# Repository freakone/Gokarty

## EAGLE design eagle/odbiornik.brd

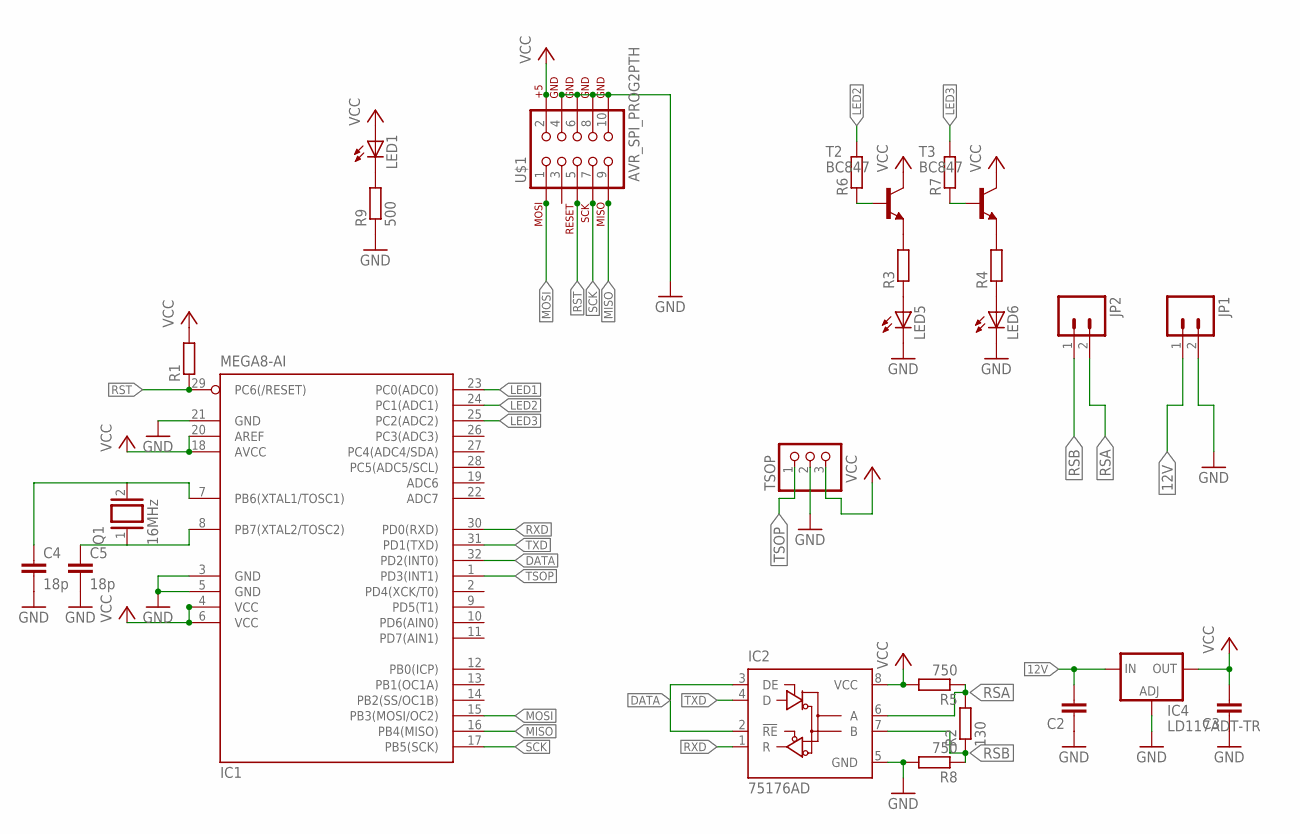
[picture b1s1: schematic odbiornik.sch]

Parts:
C2, C3: C-EUC0805; C0805
C4, C5: 18p; C0805
IC1: MEGA8-AI; TQFP32-08
IC2: 75176AD; D_R-PDSO-G8
IC4: LD117ADT-TR; DPACK
JP1, JP2: M02LOCK_LONGPADS; 1X02_LOCK_LONGPADS
LED1: LED1206; LED-1206
LED5, LED6: LEDSFH480; SFH480
Q1: 16MHz; QS
R1, R3, R4, R6, R7: R-EU_R0805; R0805
R2: 130; R0805
R5, R8: 750; R0805
R9: 500; R0805
T2, T3: BC847; SOT23
TSOP: PINHD-1X3; 1X03
U$1: AVR_SPI_PROG2PTH; AVR_ICSP

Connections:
12V: C2.2, IC4.3 (IN), JP1.1
DATA: IC1.32 (PD2(INT0)), IC2.2 (!RE), IC2.3 (DE)
GND: C2.1, C3.1, C4.2, C5.2, IC1.3 (GND), IC1.5 (GND), IC1.21 (GND), IC2.5 (GND), IC4.1 (ADJ), JP1.2, LED5.K (C), LED6.K (C), R8.2, R9.1, TSOP.2, U$1.4, U$1.6, U$1.8, U$1.10
LED1: IC1.23 (PC0(ADC0))
LED2: IC1.24 (PC1(ADC1)), R6.2
LED3: IC1.25 (PC2(ADC2)), R7.2
MISO: IC1.16 (PB4(MISO)), U$1.9
MOSI: IC1.15 (PB3(MOSI/OC2)), U$1.1
unnamed: LED1.C, R9.2
unnamed: LED5.A, R3.1
unnamed: LED6.A, R4.1
unnamed: R3.2, T2.2 (E)
unnamed: R4.2, T3.2 (E)
unnamed: R6.1, T2.1 (B)
unnamed: R7.1, T3.1 (B)
unnamed: C5.1, IC1.8 (PB7(XTAL2/TOSC2)), Q1.1
unnamed: C4.1, IC1.7 (PB6(XTAL1/TOSC1)), Q1.2
RSA: IC2.6 (A), JP2.2, R2.2, R5.1
RSB: IC2.7 (B), JP2.1, R2.1, R8.1
RST: IC1.29 (PC6(/RESET)), R1.1, U$1.5
RXD: IC1.30 (PD0(RXD)), IC2.1 (R)
SCK: IC1.17 (PB5(SCK)), U$1.7
TSOP: IC1.1 (PD3(INT1)), TSOP.1
TXD: IC1.31 (PD1(TXD)), IC2.4 (D)
VCC: C3.2, IC1.4 (VCC), IC1.6 (VCC), IC1.18 (AVCC), IC1.20 (AREF), IC2.8 (VCC), IC4.4 (OUT), LED1.A, R1.2, R5.2, T2.3 (C), T3.3 (C), TSOP.3, U$1.2

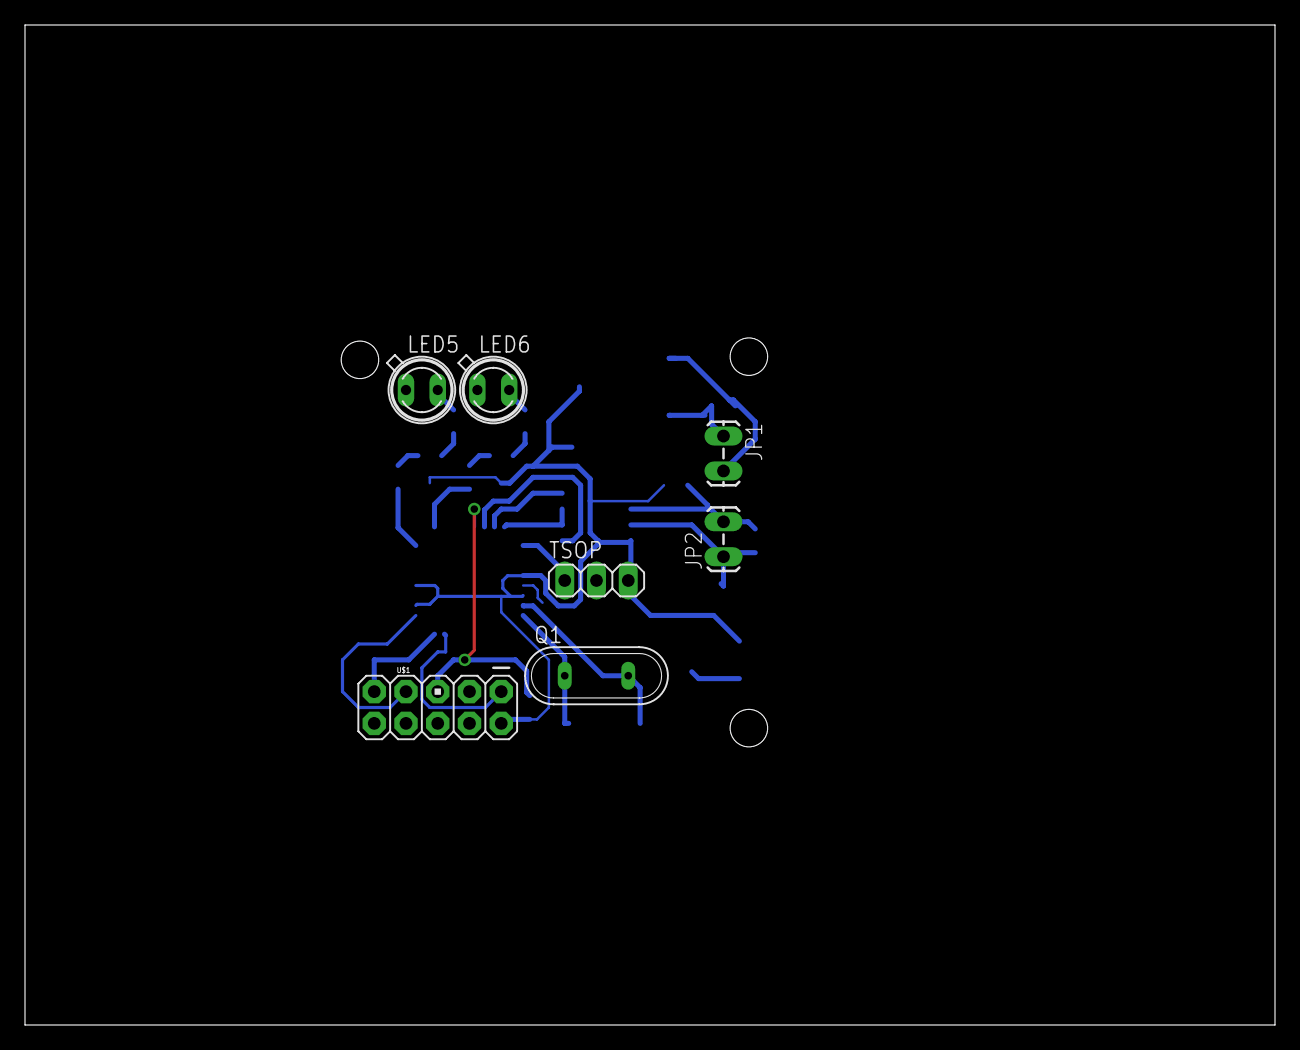
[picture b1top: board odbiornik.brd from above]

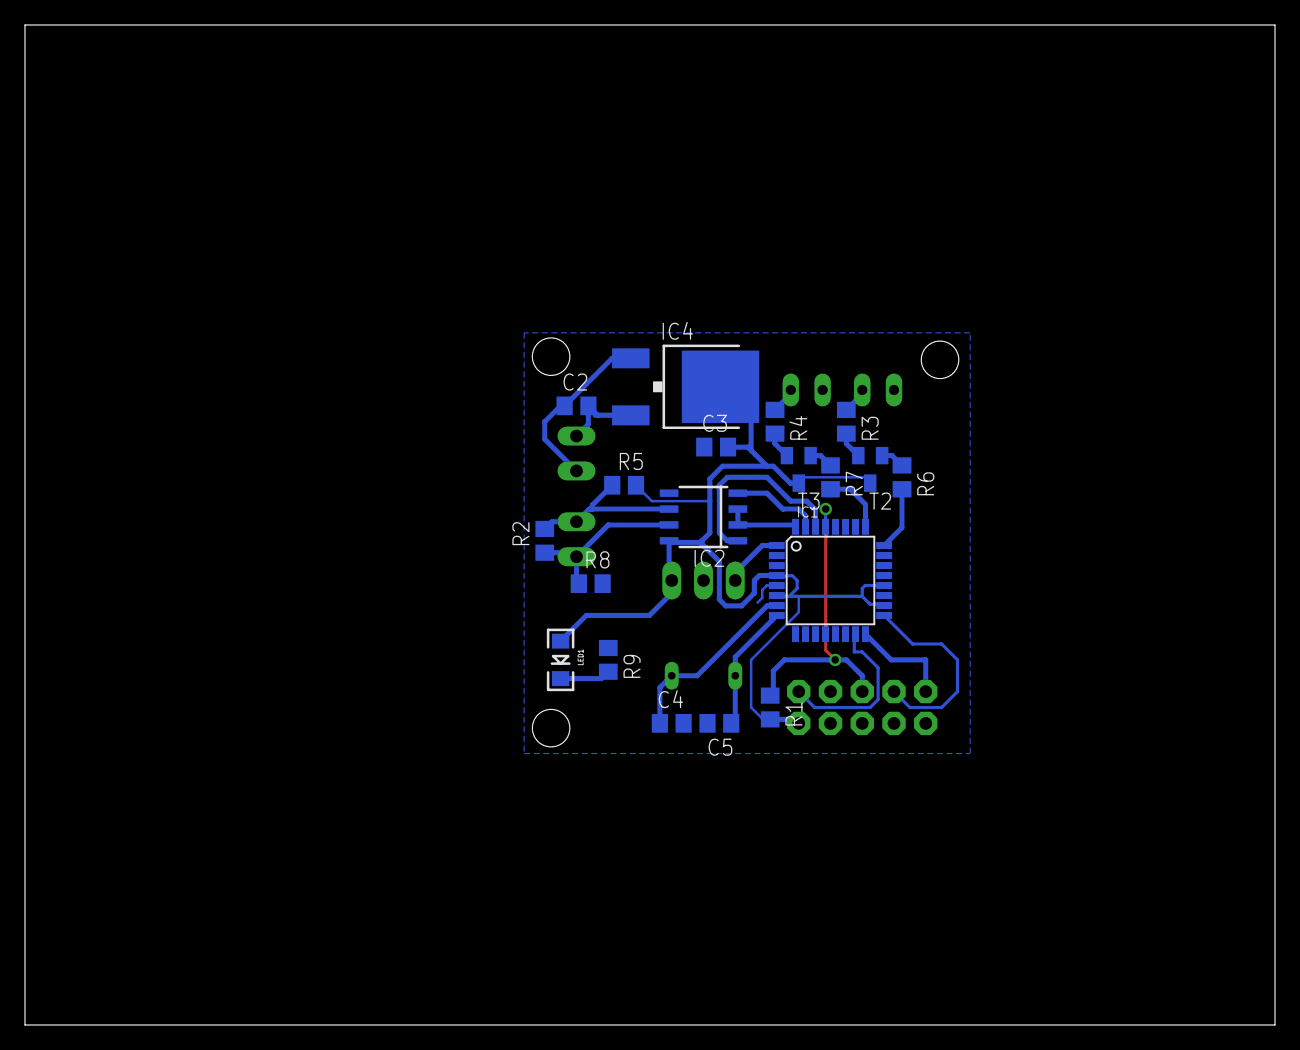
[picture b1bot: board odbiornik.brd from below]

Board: 2 copper layers, 100.0 x 80.0 mm, 26 parts (19 on the bottom side), 24 nets.

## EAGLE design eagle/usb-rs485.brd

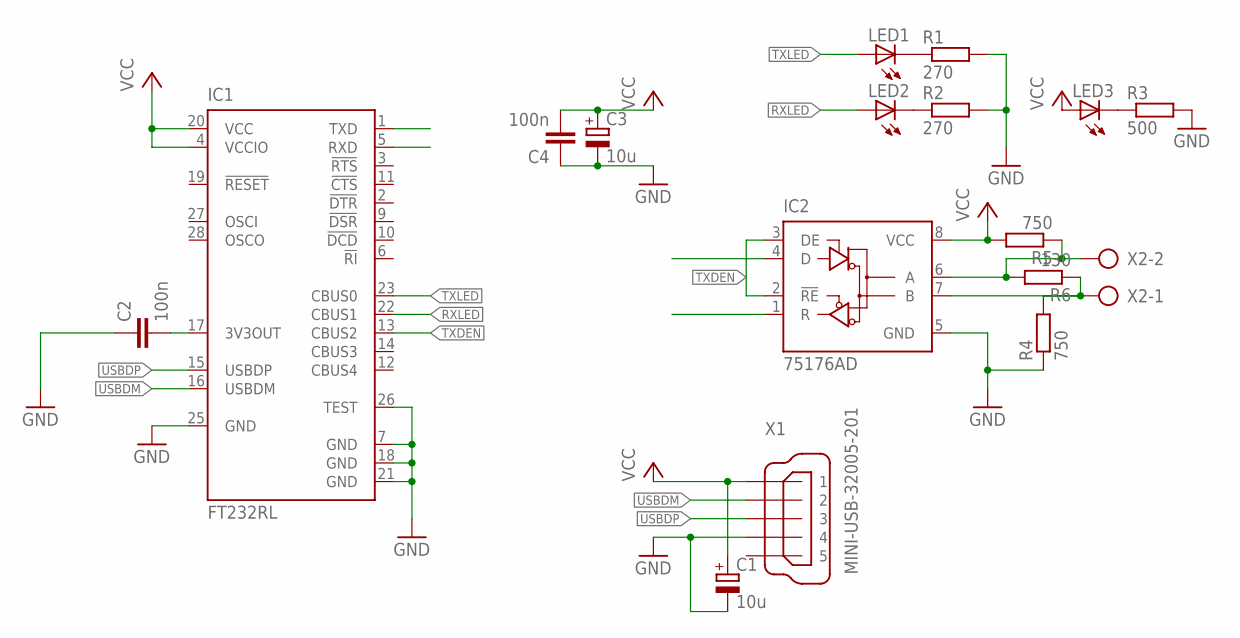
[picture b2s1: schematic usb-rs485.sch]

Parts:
C1, C3: 10u; PANASONIC_D
C2, C4: 100n; C0805
IC1: FT232RL; SSOP28
IC2: 75176AD; D_R-PDSO-G8
LED1, LED2, LED3: LEDSML0805; SML0805
R1, R2: 270; R0805
R3: 500; R0805
R4, R5: 750; R0805
R6: 130; R0805
X1: MINI-USB-32005-201; 32005-201
X2: AK300/2

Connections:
GND: C1.-, C2.1, C3.-, C4.1, IC1.7 (GND), IC1.18 (GND), IC1.21 (GND), IC1.25 (GND), IC1.26 (TEST), IC2.5 (GND), R1.2, R2.2, R3.2, R4.1, X1.4
unnamed: LED1.C, R1.1
unnamed: LED2.C, R2.1
unnamed: C2.2, IC1.17 (3V3OUT)
unnamed: LED3.C, R3.1
unnamed: IC2.6 (A), R5.1, R6.2, X2.2
unnamed: IC2.7 (B), R4.2, R6.1, X2.1
RX: IC1.5 (RXD), IC2.1 (R)
RXLED: IC1.22 (CBUS1), LED2.A
TX: IC1.1 (TXD), IC2.4 (D)
TXDEN: IC1.13 (CBUS2), IC2.2 (!RE), IC2.3 (DE)
TXLED: IC1.23 (CBUS0), LED1.A
USBDM: IC1.16 (USBDM), X1.2
USBDP: IC1.15 (USBDP), X1.3
VCC: C1.+, C3.+, C4.2, IC1.4 (VCCIO), IC1.20 (VCC), IC2.8 (VCC), LED3.A, R5.2, X1.1

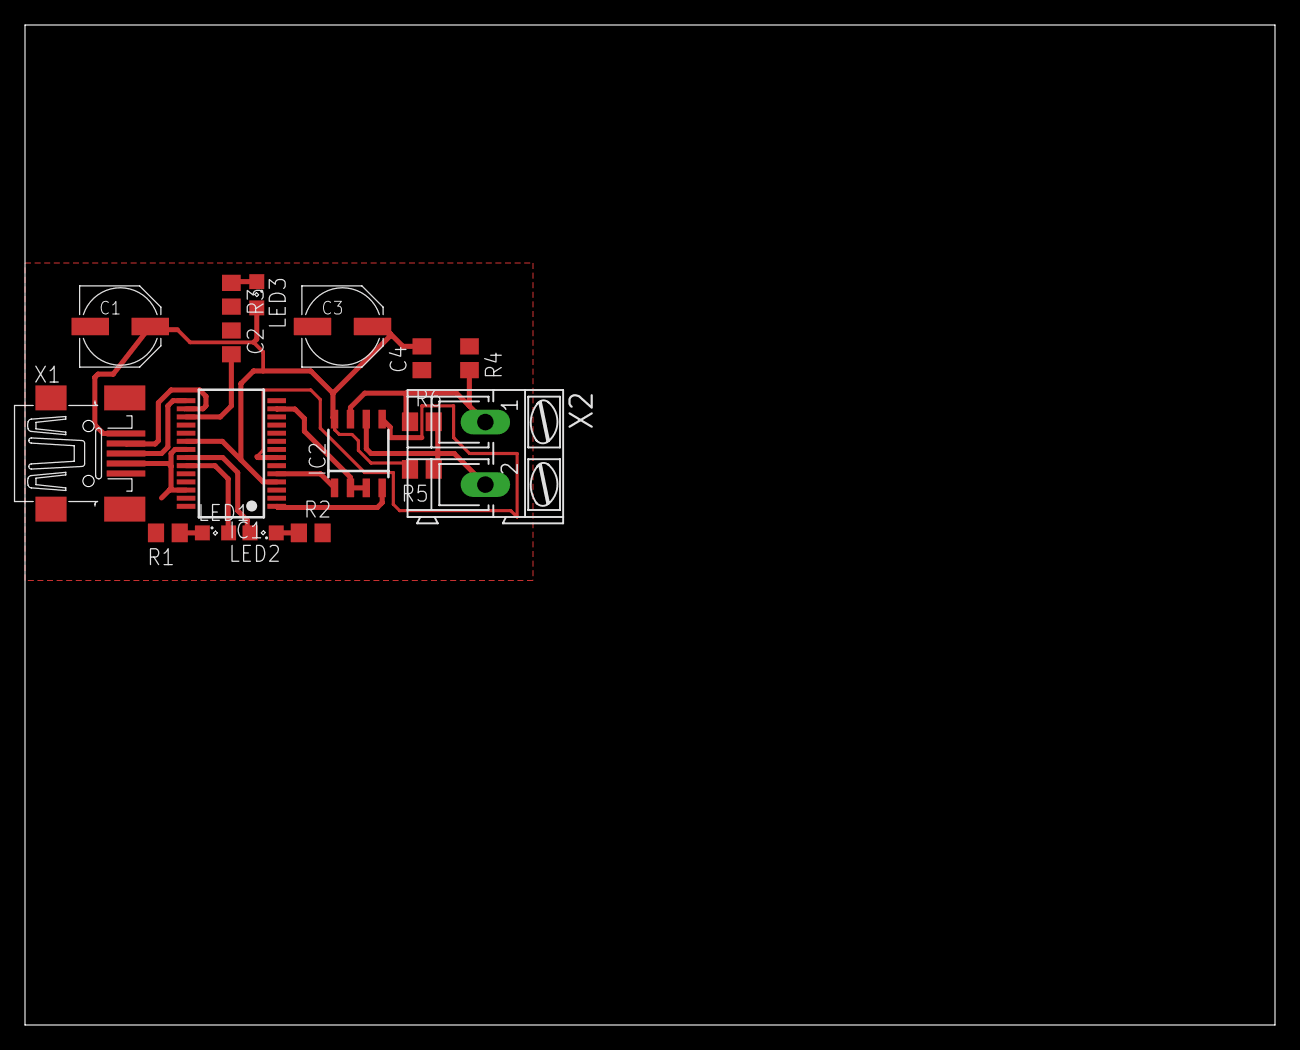
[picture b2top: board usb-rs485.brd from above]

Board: 2 copper layers, 100.0 x 80.0 mm, 17 parts (0 on the bottom side), 15 nets.

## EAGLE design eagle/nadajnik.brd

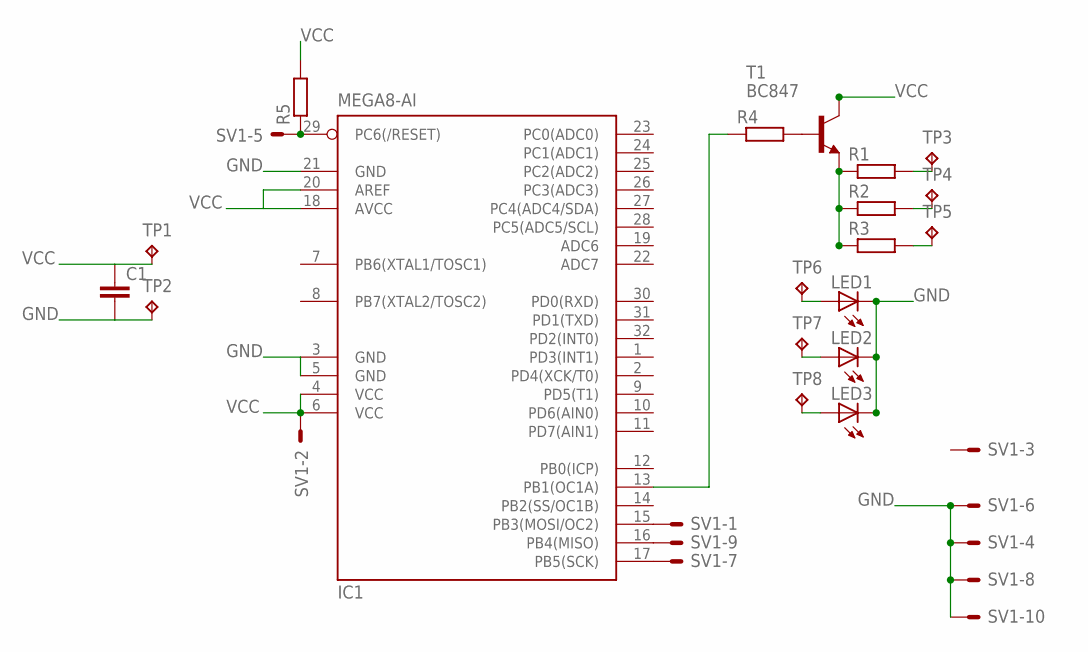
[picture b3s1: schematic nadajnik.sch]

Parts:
C1: C-EUC1206; C1206
IC1: MEGA8-AI; TQFP32-08
LED1, LED2, LED3: LEDSFH480; SFH480
R1, R2, R3, R4, R5: R-EU_R1206; R1206
SV1: ML10E; ML10
T1: BC847; SOT23
TP1, TP2, TP3, TP4, TP5, TP6, TP7, TP8: TPPAD1-13Y; P1-13Y

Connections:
GND: C1.2, IC1.3 (GND), IC1.5 (GND), IC1.21 (GND), LED1.K (C), LED2.K (C), LED3.K (C), SV1.4, SV1.6, SV1.8, SV1.10, TP2.TP
unnamed: R1.2, TP3.TP
unnamed: R2.2, TP4.TP
unnamed: R3.2, TP5.TP
unnamed: IC1.13 (PB1(OC1A)), R4.1
unnamed: R4.2, T1.1 (B)
unnamed: R1.1, R2.1, R3.1, T1.2 (E)
unnamed: LED1.A, TP6.TP
unnamed: LED2.A, TP7.TP
unnamed: LED3.A, TP8.TP
unnamed: IC1.15 (PB3(MOSI/OC2)), SV1.1
unnamed: IC1.29 (PC6(/RESET)), R5.1, SV1.5
unnamed: IC1.16 (PB4(MISO)), SV1.9
unnamed: IC1.17 (PB5(SCK)), SV1.7
VCC: C1.1, IC1.4 (VCC), IC1.6 (VCC), IC1.18 (AVCC), IC1.20 (AREF), R5.2, SV1.2, T1.3 (C), TP1.TP

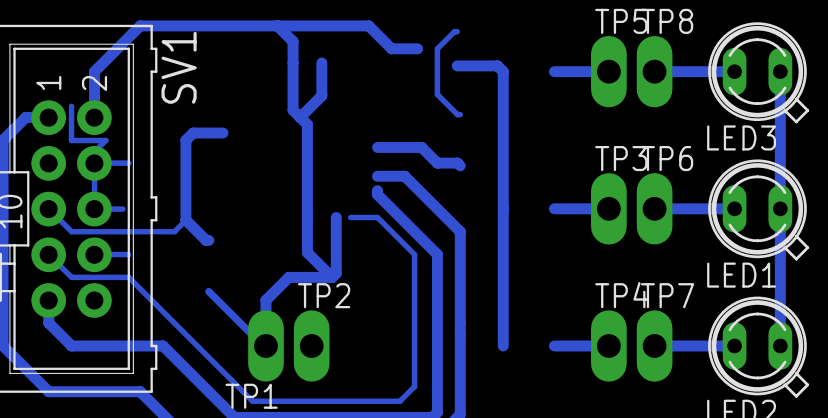
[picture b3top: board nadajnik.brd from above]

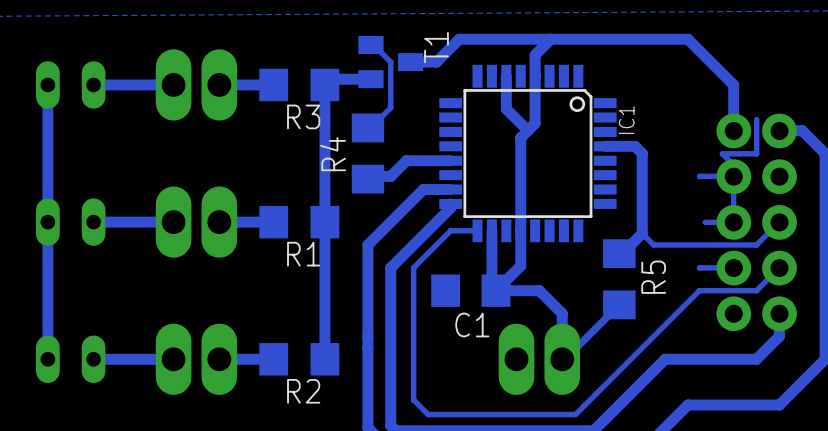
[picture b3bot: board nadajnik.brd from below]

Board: 2 copper layers, 20 parts (8 on the bottom side), 15 nets.

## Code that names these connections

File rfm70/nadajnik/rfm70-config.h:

/*
	Biblioteka RFM70 dla AVR'ów oparta na projekcie Daniela z http:://projects.web4clans.com
	
	Autor: freakone
	WWW: freakone.pl
	@: kamil@freakone.pl
*/

#include "uart.h" // jeli chcemy korzystaæ z uarta
#define DEBUG 1 // jeli chcemy debugowaæ - uart równie¿ musi byæ zainkludowany

//RFM70
#define DDR_SPI DDRB
#define PORT_SPI PORTB
#define SCK  PB7
#define MISO PB6
#define MOSI PB5
#define CE   PB4
#define CSN  PB3

//DIODA
#define DDR_BLINK DDRD
#define PORT_BLINK PORTD
#define BLINK PD7

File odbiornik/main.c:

#include <avr/io.h>
#include <util/delay.h>
#include <avr/interrupt.h>



void USARTWriteChar(char data)
{
   PORTD |= (1<<2);
   while(!(UCSRA & (1<<UDRE)));
   UDR=data;
}

unsigned char USARTReadChar( void ) {
	PORTD &= ~(1<<2);
	while ( !(UCSRA & (1<<RXC)) );
	return UDR;
}

void code_recognized(unsigned int cmd)
{
	if(cmd == 11)
    {  
		PORTC |= (1 << PC1);		
	}
	
	if(cmd == 20)
    {  
		PORTC |= (1 << PC0);		
	}
	
	
	USARTWriteChar((char)cmd);
}

ISR(INT1_vect)
{
   static unsigned char n, pb;
   static unsigned int code;
  
   switch(n)
   {
      case 0:

         if(MCUCR&(1<<ISC10))
         {
            MCUCR &= ~(1<<ISC10);
	    TCNT0 = 0x00; TIFR |= (1<<TOV0);
         }
         else 
         {
	    if((TCNT0>112)||(TIFR&(1<<TOV0))) // 112 = 3,6ms
	    {	    
               pb=0;	    
	       code = 0x03;
               TCNT0  = 0x00; TIFR |= (1<<TOV0);
               n = 1;
	    }
            MCUCR |= (1<<ISC10);
	 }
      break;

      case 1:
      case 2:	
         if((TCNT0>14)&&(TCNT0<42))  // 14 = 0.4ms, 42 = 1.35ms
	 {
            MCUCR ^= (1<<ISC10);
            TCNT0  = 0x00; TIFR |= (1<<TOV0);
	    n++;
	 }
	 else n = 0;

      break;

      default:  
    
         if((TCNT0>14)&&(TCNT0<42))
	 {
             if(!pb)
             {		     
	        pb = 1;
                code <<= 1;
		if(code&0x2) code |= 1;
             }
	     else
             {
                pb = 0;
		n++;
	     }

	     TCNT0 = 0x00; TIFR |= (1<<TOV0);
	 }
	 else if((TCNT0>42)&&(TCNT0<70)) // 70=2.25ms
	 {
             code <<= 1;
	     if(!(code&0x2)) code |= 1;

	     TCNT0 = 0x00; TIFR |= (1<<TOV0);
             n++;
	 }
         else  n = 0;		 

         MCUCR ^= (1<<ISC10);

	 if(n==9)
	 {
	     n = 0;
		 code = code & ~(3 << 6);
		 code_recognized(code);
	 }

      break;
   }
   
   
}


void USARTInit(uint16_t ubrr_value)
{
   

   UBRRL = ubrr_value;
   UBRRH = (ubrr_value>>8);

   /*Set Frame Format
   >> Asynchronous mode
   >> No Parity
   >> 1 StopBit
   >> char size 8
   */
   UCSRC=(1<<URSEL)|(3<<UCSZ0);

   UCSRB=(1<<RXEN)|(1<<TXEN);
}

void init_rc5(void)
{
	 DDRD  &= ~(1<<PD3); 
    PORTD &= ~(1<<PD3);
    //
    MCUCR |= (1<<ISC11); // opadajace zbocze 
    GICR  |= (1<<INT1);	
    //
    TCCR0 = (1<<CS02); // prescaler 256
    TIFR |= (1<<TOV0);    

    sei();
}

int main(void)
{
  volatile unsigned int cmd;
  volatile unsigned int i1 = 0, i2 = 0;

  DDRD = (1 << PD2) | (1 << PD1); //RX+DATA pin init
  DDRD &= ~(1<<0); //TX
  DDRC = 0xff;
  init_rc5(); 
  USARTInit(51);

  while (1)
  {			
	if(PORTC & (1 << PC1))
		i2++;
		
	if(PORTC & (1 << PC0))
		i1++;
		
	if(i2 > 100)
	{
		PORTC &= ~(1 << PC1);	
		i2 = 0;
	}
	
	if(i1 > 100)
	{
		PORTC &= ~(1 << PC0);	
		i1 = 0;
	}
	
	_delay_ms(50);
  }

  return 0;
}

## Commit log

2013-03-14 pierwsza wersja kodu nadajnika
2013-03-15 działający nadajnik i odbiornik
2013-03-15 lekki porządek
2013-03-15 test - kisieel
2013-03-15 płytki i rozpoznawanie 2 kodów
2013-03-15 Dodano wysyłanie danych RS485 - działa w jedną stronę.
2013-03-15 test do 10 nadajnikow (1-bajtowe kody)
2013-03-17 miljon zmian!
    - libka do rfma
    - zmiana protokołu: wywalone toggle bity, kod skrócony do 6 bitów + 2
    startowe = 8, 2 razy krótsza komunikacja
    - odbiornik na przerwaniach, razem ze skróconym proto chodzi z 10 razy
    szybciej
    - kod pod testy dwóch rozwiązań
2013-03-18 Zmiany: Odbiornik +Polaryzacja +Terminator +Poprawki TSOP +ISP Socket +Power LED Dodano: RS485<->USB - v. poprawiona
2013-03-19 New Receiver Board + Schematic + Gitignore prototype

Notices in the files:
parts and their libraries:
SparkFun-Connectors: Licensing: CC v3.0 Share-Alike You are welcome to use this library for commercial purposes.
